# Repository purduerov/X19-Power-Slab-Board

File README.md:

# Purdue ROV KiCad Board Template

Starter template for new PCB designs in Purdue ROV. Pre-configured with the team component library submodule, automatic Git clean filters, isolation rules, and CI/CD validation.

---

## 🚀 Quickstart: Opening the Project (Recommended)

**Always open the project using the 1-click launcher:**

* **Windows:** Double-click `LAUNCH_KICAD.bat`
* **macOS / Linux:** Run `./LAUNCH_KICAD.sh`

### What the Launcher Does Automatically:
1. ⚙️ **Configures Git Hooks & Clean Filters:** Sets up Git to strip volatile viewport/zoom coordinates on every commit, preventing merge conflicts.
2. 🔄 **Auto-Updates Component Library:** Pulls the freshest symbols, footprints, and 3D models from `purdue-rov-kicad-lib` before opening.
3. 📐 **Opens KiCad:** Launches the project file with all 6 central library categories pre-linked.

---

## Creating a New Board Repository

1. In GitHub, click **Use this template** > **Create a new repository**.
2. Name the repo to match the board function (e.g. `thruster-interface-board`).
3. Clone recursively so submodules are pulled:
   ```bash
   git clone --recursive https://github.com/purduerov/<your-repo-name>.git
   cd <your-repo-name>
   ```
   If cloned without `--recursive`, initialize the submodule:
   ```bash
   git submodule update --init --recursive
   ```

4. Rename the project files (`board-template.kicad_*`) to match your project name.

## Central Component Library & Manager GUI

The template is pre-configured with project-level library tables (`sym-lib-table` and `fp-lib-table`) pointing to `purdue-rov-kicad-lib`:
- `rov_passives`: Resistors, capacitors, inductors, crystals
- `rov_power`: Voltage regulators, buck/boost converters, MOSFETs, diodes
- `rov_logic`: MCUs, logic ICs, op-amps, level shifters, transceivers
- `rov_connectors`: Power terminals, XT60/XT30, headers, USB, JST connectors
- `rov_sensors`: IMUs, temperature, pressure sensors
- `rov_mech`: Mounting holes, standoffs, test points

### Launching the Library Manager GUI
To browse parts, inspect footprints, edit properties, or add/delete components in the shared library:
- **Windows:** Double-click `libs\purdue-rov-kicad-lib\LIBRARY_MANAGER.bat`
- **macOS / Linux:** Run `./libs/purdue-rov-kicad-lib/LIBRARY_MANAGER.sh`

## Design Rules & Clearances

- Clearance rules (JLCPCB 4-layer rules) are defined in `X19-Power-Slab-Board.kicad_dru`.
- High-power thruster nets require a minimum 2.0 mm clearance from low-voltage logic (3.3V / 5V).

## Automated CI/CD & DevOps Preflight Checks

All CI/CD automation and tooling are centralized in [`purduerov/pcb-devops`](https://github.com/purduerov/pcb-devops):
1. **Automated Git Clean Filters:** Configured automatically by `.githooks/pre-commit` to prevent viewport/zoom merge noise.
2. **KiCad Symbol Linting:** Validates mandatory fields (`MPN`, `Manufacturer`, `Category`, `DigiKey`, `Datasheet`, `Temp_Range`) on all library components.
3. **ERC & DRC Validation:** Executes Electrical and Design Rules Checks via KiBot in GitHub Actions.
4. **Artifact Generation:** Automatically exports Schematic PDFs, Board Layout PDFs, and Interactive HTML BOMs on every pull request.

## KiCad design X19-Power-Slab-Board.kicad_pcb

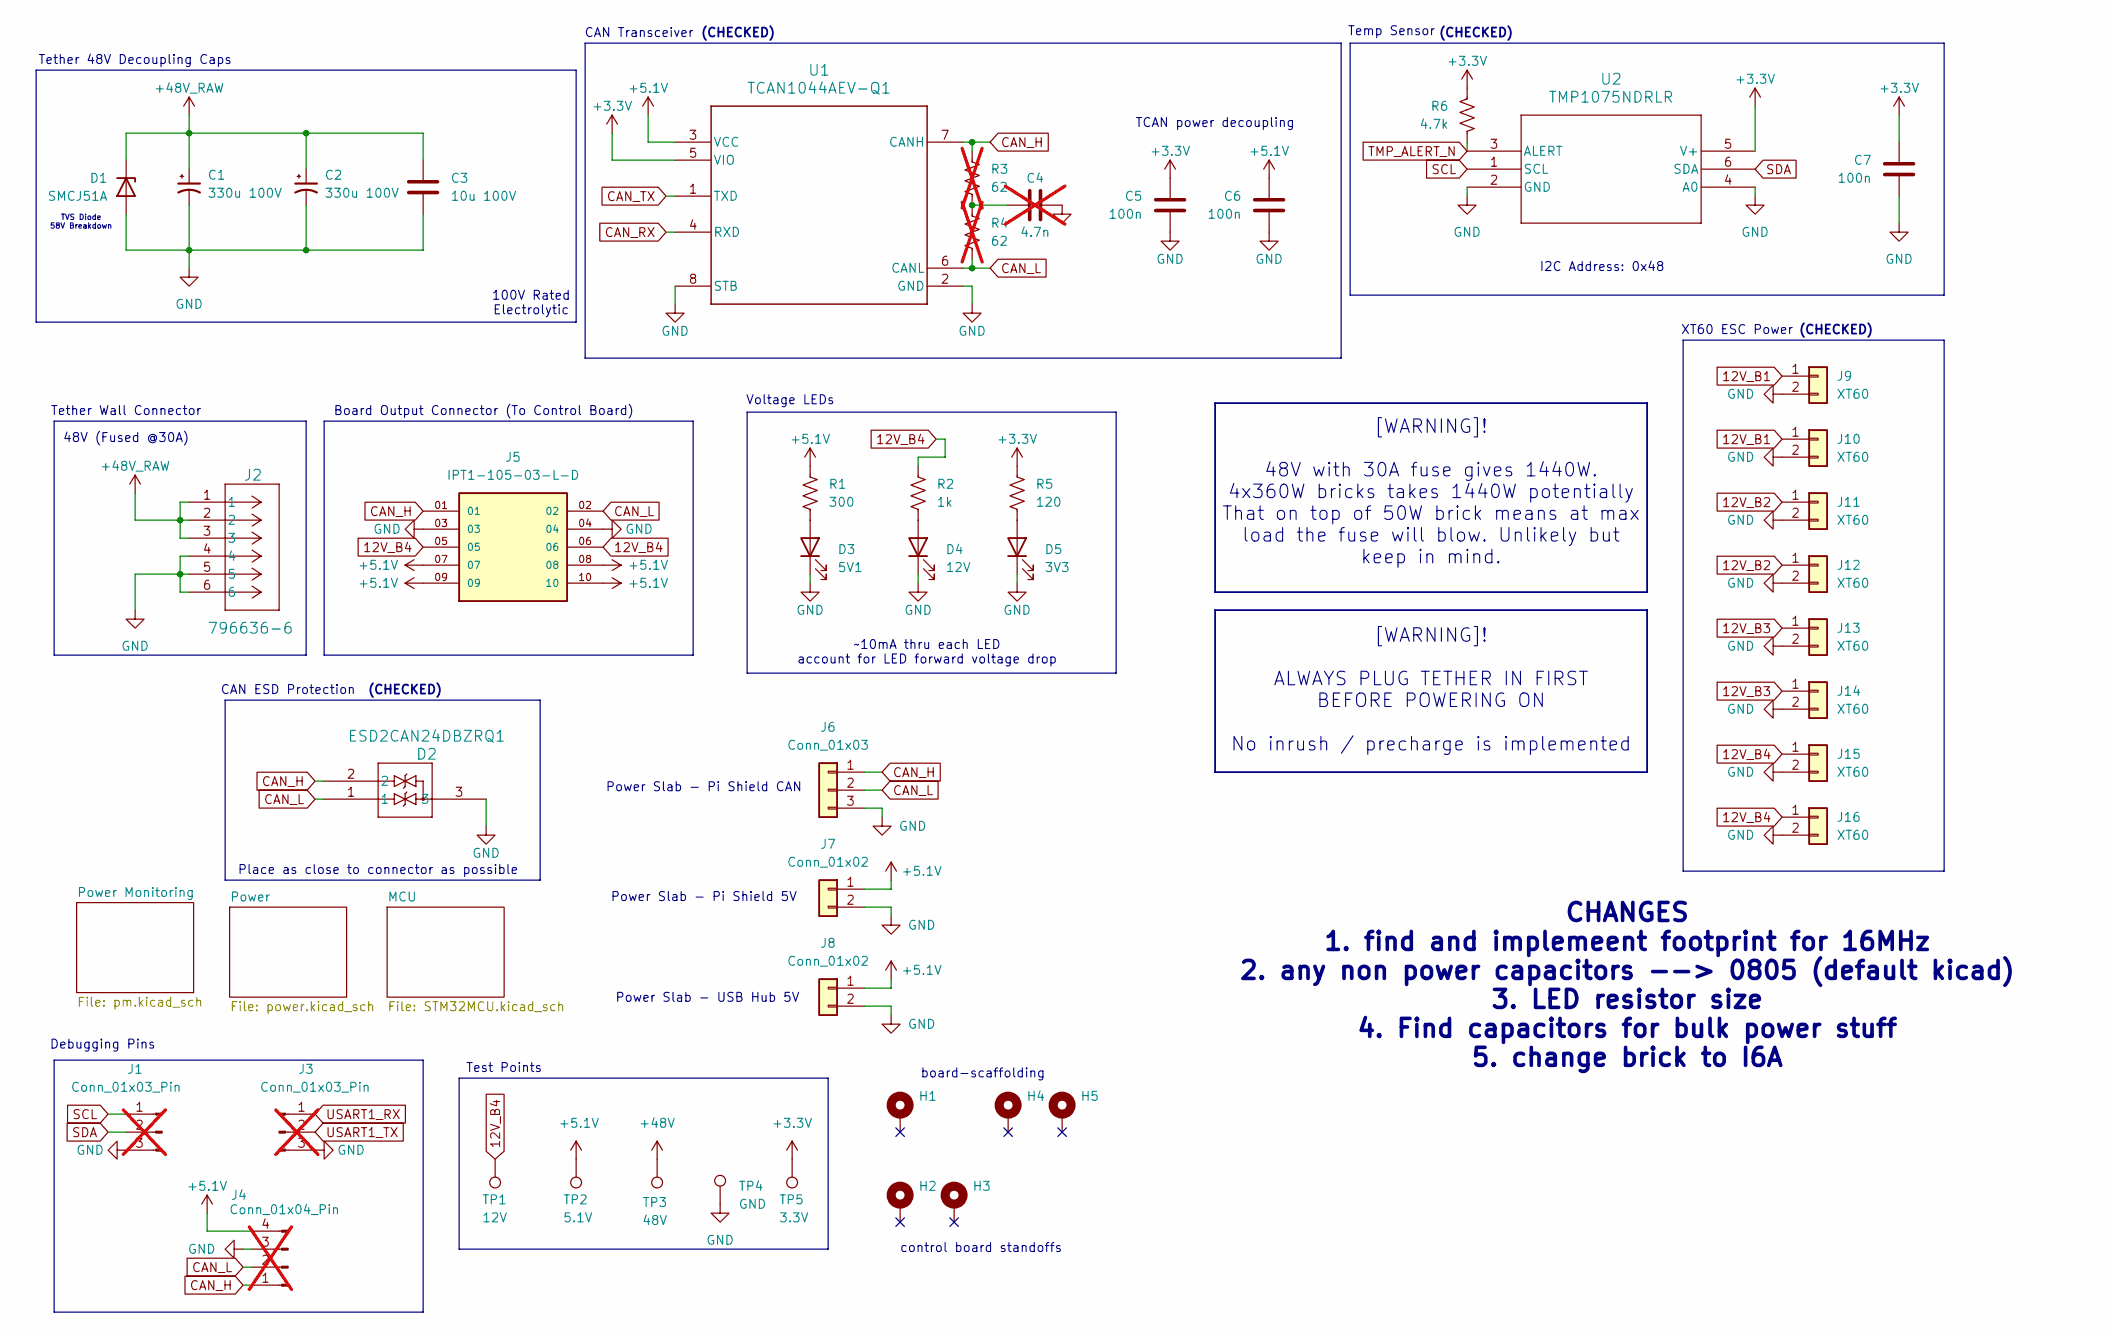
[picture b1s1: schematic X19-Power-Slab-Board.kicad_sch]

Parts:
C1, C2: 330u 100V; CP_Radial_D13.0mm_P5.00mm; Part Number 860040878008
C3: 10u 100V; C_1210_3225Metric; Part Number GMC32X7R106K100NT
C4: 4.7n; C_0603_1608Metric_Pad1.08x0.95mm_HandSolder; Part Number CC0603KRX7R9BB472; not fitted
C5, C6, C7: 100n; C_0603_1608Metric_Pad1.08x0.95mm_HandSolder; Part Number CC0603KRX7R8BB104
D1: SMCJ51A; D_SMC; Part Number SMCJ51A
D2: ESD2CAN24DBZRQ1; SOT-23_Handsoldering; Part Number ESD2CAN24DBZRQ1
D3: 5V1; LED_0603_1608Metric_Pad1.05x0.95mm_HandSolder; Part Number LTST-C190GKT
D4: 12V; LED_0603_1608Metric_Pad1.05x0.95mm_HandSolder; Part Number LTST-C190KRKT
D5: 3V3; LED_0603_1608Metric_Pad1.05x0.95mm_HandSolder; Part Number LTST-C190YKT
H1, H4, H5: MountingHole_Pad; MountingHole_3.5mm_Pad
H2, H3: MountingHole_Pad; MountingHole_2.7mm_M2.5_Pad
J1, J3: Conn_01x03_Pin; PinHeader_1x03_P2.54mm_Vertical; Part Number Generic 2.54mm Pinheader; not fitted
J2: 796636-6; CON6_P5MM_VER_TERM-BLK_TYC; Part Number 796636-6
J4: Conn_01x04_Pin; PinHeader_1x04_P2.54mm_Vertical; Part Number Generic 2.54mm Pinheader; not fitted
J5: IPT1-105-03-L-D; SAMTEC_IPT1-105-01-S-D; PARTREV R
J6: Conn_01x03; Molex_Micro-Fit_3.0_43650-0300_1x03_P3.00mm_Horizontal; Part Number 43650-0300
J7, J8: Conn_01x02; Molex_Micro-Fit_3.0_43650-0200_1x02_P3.00mm_Horizontal; Part Number 43650-0200
J9, J10, J11, J12, J13, J14, J15, J16: XT60; AMASS_XT60PB-M; Part Number 1568-10474-ND
R1: 300; R_0603_1608Metric_Pad0.98x0.95mm_HandSolder; Part Number RC0603FR-07300RL
R2: 1k; R_0603_1608Metric_Pad0.98x0.95mm_HandSolder; Part Number RC0603FR-071KL
R3, R4: 62; R_0603_1608Metric_Pad0.98x0.95mm_HandSolder; Part Number RC0603FR-0762RL; not fitted
R5: 120; R_0603_1608Metric_Pad0.98x0.95mm_HandSolder; Part Number RC0603FR-07120RL
R6: 4.7k; R_0603_1608Metric_Pad0.98x0.95mm_HandSolder; Part Number RC0603FR-074K7L
TP1: 12V; TestPoint_Pad_D4.0mm
TP2: 5.1V; TestPoint_Pad_D2.5mm
TP3: 48V; TestPoint_Pad_D4.0mm
TP4: GND; TestPoint_Pad_D2.5mm
TP5: 3.3V; TestPoint_Pad_D2.5mm
U1: TCAN1044AEV-Q1; SOIC-8_3.9x4.9mm_P1.27mm; Part Number TCAN1044AEVDRQ1
U2: TMP1075NDRLR; SOT5X3-6_DRL_TEX; Part Number TMP1075NDRLR

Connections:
12V_B1: J9.1, J10.1; also elsewhere on the board
12V_B2: J11.1, J12.1; also elsewhere on the board
12V_B3: J13.1, J14.1; also elsewhere on the board
12V_B4: J5.05, J5.06, J15.1, J16.1, R2.2, TP1.1 (1_1); also elsewhere on the board
+3.3V: C5.1, C7.1, R5.2, R6.1, TP5.1 (1_1), U1.5 (VIO), U2.5 (V+); also elsewhere on the board
+5.1V: C6.1, J4.4, J5.07, J5.08, J5.09, J5.10, J7.1, J8.1, R1.2, TP2.1 (1_1), U1.3 (VCC); also elsewhere on the board
+48V: TP3.1 (1_1); also elsewhere on the board
+48V_RAW: C1.1, C2.1, C3.1, D1.1 (K), J2.1, J2.2, J2.3; also elsewhere on the board
CAN_H: D2.2, J4.1, J5.01, J6.1, R3.1, U1.7 (CANH)
CAN_L: D2.1, J4.2, J5.02, J6.2, R4.2, U1.6 (CANL)
CAN_RX: U1.4 (RXD); also elsewhere on the board
CAN_TX: U1.1 (TXD); also elsewhere on the board
GND: C1.2, C2.2, C3.2, C4.2, C5.2, C6.2, C7.2, D1.2 (A), D2.3, D3.1 (K), D4.1 (K), D5.1 (K), J1.3, J2.4, J2.5, J2.6, J3.3, J4.3, J5.03, J5.04, J6.3, J7.2, J8.2, J9.2, J10.2, J11.2, J12.2, J13.2, J14.2, J15.2, J16.2, TP4.1 (1_1), U1.2 (GND), U1.8 (STB), U2.2 (GND), U2.4 (A0); also elsewhere on the board
unnamed: C4.1, R3.2, R4.1
unnamed: D3.2 (A), R1.1
unnamed: D4.2 (A), R2.1
unnamed: D5.2 (A), R5.1
SCL: J1.1, U2.1 (SCL); also elsewhere on the board
SDA: J1.2, U2.6 (SDA); also elsewhere on the board
TMP_ALERT_N: R6.2, U2.3 (ALERT); also elsewhere on the board
USART1_RX: J3.1; also elsewhere on the board
USART1_TX: J3.2; also elsewhere on the board

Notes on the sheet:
TCAN power decoupling
(CHECKED)
100V Rated Electrolytic
XT60 ESC Power
CAN Transceiver
control board standoffs
I2C Address: 0x48
Power Slab - Pi Shield CAN
[WARNING]! 48V with 30A fuse gives 1440W. 4x360W bricks takes 1440W potentially That on top of 50W brick means at max load the fuse will blow. Unlikely but keep in mind.
Place as close to connector as possible
Temp Sensor
Board Output Connector (To Control Board)
TVS Diode 58V Breakdown
~10mA thru each LED account for LED forward voltage drop
CAN ESD Protection
Tether 48V Decoupling Caps
Voltage LEDs
CHANGES 1. find and implemeent footprint for 16MHz 2. any non power capacitors --> 0805 (default kicad) 3. LED resistor size 4. Find capacitors for bulk power stuff 5. change brick to I6A
[WARNING]! ALWAYS PLUG TETHER IN FIRST BEFORE POWERING ON No inrush / precharge is implemented
board-scaffolding
Test Points
Debugging Pins
Power Slab - USB Hub 5V
Tether Wall Connector
48V (Fused @30A)
Power Slab - Pi Shield 5V

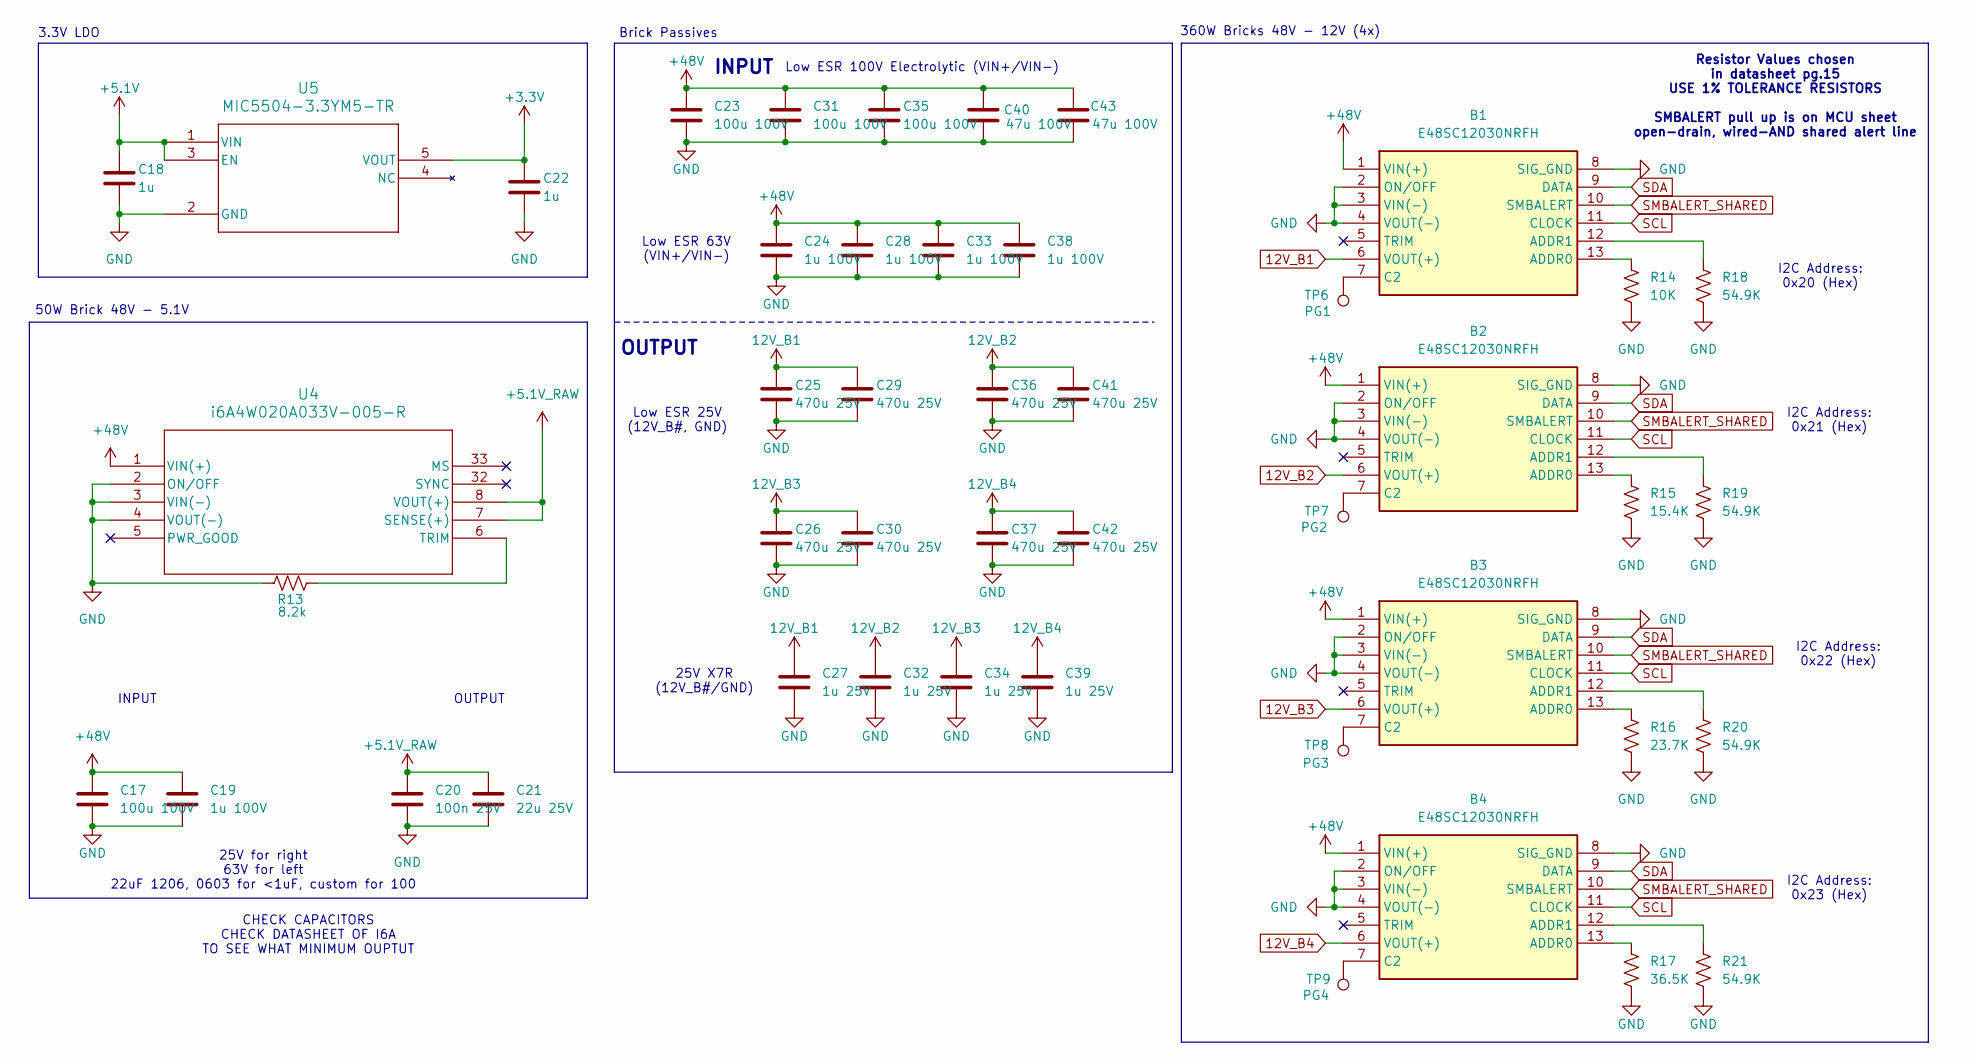
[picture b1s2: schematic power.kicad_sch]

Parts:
B1, B2, B3, B4: E48SC12030NRFH; Manufacturer_Part_Number E48SC12030NRFH
C17, C23, C31, C35: 100u 100V; CP_Radial_D10.0mm_P5.00mm; Part Number 100ZLH100MEFC10X20
C18, C22: 1u; C_0603_1608Metric_Pad1.08x0.95mm_HandSolder; Part Number CC0603KRX5R6BB105
C19, C24, C28, C33, C38: 1u 100V; C_0805_2012Metric_Pad1.18x1.45mm_HandSolder; Part Number CGA4J3X7S2A105M125AE
C20: 100n 25V; C_0603_1608Metric_Pad1.08x0.95mm_HandSolder; Part Number CC0603KRX7R8BB104
C21: 22u 25V; C_1206_3216Metric_Pad1.33x1.80mm_HandSolder; Part Number CC1206KKX5R8BB226
C25, C26, C29, C30, C36, C37, C41, C42: 470u 25V; CP_Radial_D10.0mm_P5.00mm; Part Number 25CZJ470M10X9
C27, C32, C34, C39: 1u 25V; C_0805_2012Metric_Pad1.18x1.45mm_HandSolder; Part Number CC0805KKX7R8BB105
C40, C43: 47u 100V; CP_Radial_D10.0mm_P5.00mm; Part Number UVZ2A470MPD
R13: 8.2k; R_0603_1608Metric_Pad0.98x0.95mm_HandSolder; Part Number RC0603FR-078K2L
R14: 10K; R_0603_1608Metric_Pad0.98x0.95mm_HandSolder; Part Number RC0603FR-0710KL
R15: 15.4K; R_0603_1608Metric_Pad0.98x0.95mm_HandSolder; Part Number RC0603FR-0715K4L
R16: 23.7K; R_0603_1608Metric_Pad0.98x0.95mm_HandSolder; Part Number RC0603FR-0723K7L
R17: 36.5K; R_0603_1608Metric_Pad0.98x0.95mm_HandSolder; Part Number RC0603FR-0736K5L
R18, R19, R20, R21: 54.9K; R_0603_1608Metric_Pad0.98x0.95mm_HandSolder; Part Number RC0603FR-0754K9L
TP6: PG1; TestPoint_Pad_D2.5mm
TP7: PG2; TestPoint_Pad_D2.5mm
TP8: PG3; TestPoint_Pad_D2.5mm
TP9: PG4; TestPoint_Pad_D2.5mm
U4: i6A4W020A033V-005-R; i6A4W_DIP_FULL_TDK; Part Number i6A4W020A033V-005-R
U5: MIC5504-3.3YM5-TR; SOT-23-5; Part Number MIC5504-3.3YM5-TR

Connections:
12V_B1: B1.6 (VOUT(+)), C25.1, C27.1, C29.1; also elsewhere on the board
12V_B2: B2.6 (VOUT(+)), C32.1, C36.1, C41.1; also elsewhere on the board
12V_B3: B3.6 (VOUT(+)), C26.1, C30.1, C34.1; also elsewhere on the board
12V_B4: B4.6 (VOUT(+)), C37.1, C39.1, C42.1; also elsewhere on the board
+3.3V: C22.1, U5.5 (VOUT); also elsewhere on the board
+5.1V: C18.1, U5.1 (VIN), U5.3 (EN); also elsewhere on the board
+5.1V_RAW: C20.1, C21.1, U4.7 (SENSE(+)), U4.8 (VOUT(+)); also elsewhere on the board
+48V: B1.1 (VIN(+)), B2.1 (VIN(+)), B3.1 (VIN(+)), B4.1 (VIN(+)), C17.1, C19.1, C23.1, C24.1, C28.1, C31.1, C33.1, C35.1, C38.1, C40.1, C43.1, U4.1 (VIN(+)); also elsewhere on the board
GND: B1.2 (ON/OFF), B1.3 (VIN(-)), B1.4 (VOUT(-)), B1.8 (SIG_GND), B2.2 (ON/OFF), B2.3 (VIN(-)), B2.4 (VOUT(-)), B2.8 (SIG_GND), B3.2 (ON/OFF), B3.3 (VIN(-)), B3.4 (VOUT(-)), B3.8 (SIG_GND), B4.2 (ON/OFF), B4.3 (VIN(-)), B4.4 (VOUT(-)), B4.8 (SIG_GND), C17.2, C18.2, C19.2, C20.2, C21.2, C22.2, C23.2, C24.2, C25.2, C26.2, C27.2, C28.2, C29.2, C30.2, C31.2, C32.2, C33.2, C34.2, C35.2, C36.2, C37.2, C38.2, C39.2, C40.2, C41.2, C42.2, C43.2, R13.1, R14.2, R15.2, R16.2, R17.2, R18.2, R19.2, R20.2, R21.2, U4.2 (ON/OFF), U4.3 (VIN(-)), U4.4 (VOUT(-)), U5.2 (GND); also elsewhere on the board
unnamed: B1.13 (ADDR0), R14.1
unnamed: B1.12 (ADDR1), R18.1
unnamed: B1.7 (C2), TP6.1 (1_1)
unnamed: B2.13 (ADDR0), R15.1
unnamed: B2.12 (ADDR1), R19.1
unnamed: B2.7 (C2), TP7.1 (1_1)
unnamed: B3.13 (ADDR0), R16.1
unnamed: B3.12 (ADDR1), R20.1
unnamed: B3.7 (C2), TP8.1 (1_1)
unnamed: B4.13 (ADDR0), R17.1
unnamed: B4.12 (ADDR1), R21.1
unnamed: B4.7 (C2), TP9.1 (1_1)
unnamed: R13.2, U4.6 (TRIM)
SCL: B1.11 (CLOCK), B2.11 (CLOCK), B3.11 (CLOCK), B4.11 (CLOCK); also elsewhere on the board
SDA: B1.9 (DATA), B2.9 (DATA), B3.9 (DATA), B4.9 (DATA); also elsewhere on the board
SMBALERT_SHARED: B1.10 (SMBALERT), B2.10 (SMBALERT), B3.10 (SMBALERT), B4.10 (SMBALERT); also elsewhere on the board

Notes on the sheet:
3.3V LDO
CHECK CAPACITORS CHECK DATASHEET OF I6A TO SEE WHAT MINIMUM OUPTUT
360W Bricks 48V - 12V (4x)
Brick Passives
Low ESR 63V (VIN+/VIN-)
50W Brick 48V - 5.1V
OUTPUT
INPUT
I2C Address: 0x21 (Hex)
Low ESR 100V Electrolytic (VIN+/VIN-)
I2C Address: 0x20 (Hex)
Low ESR 25V (12V_B#, GND)
25V for right 63V for left 22uF 1206, 0603 for <1uF, custom for 100
Resistor Values chosen in datasheet pg.15 USE 1% TOLERANCE RESISTORS SMBALERT pull up is on MCU sheet open-drain, wired-AND shared alert line
25V X7R (12V_B#/GND)
I2C Address: 0x22 (Hex)
I2C Address: 0x23 (Hex)

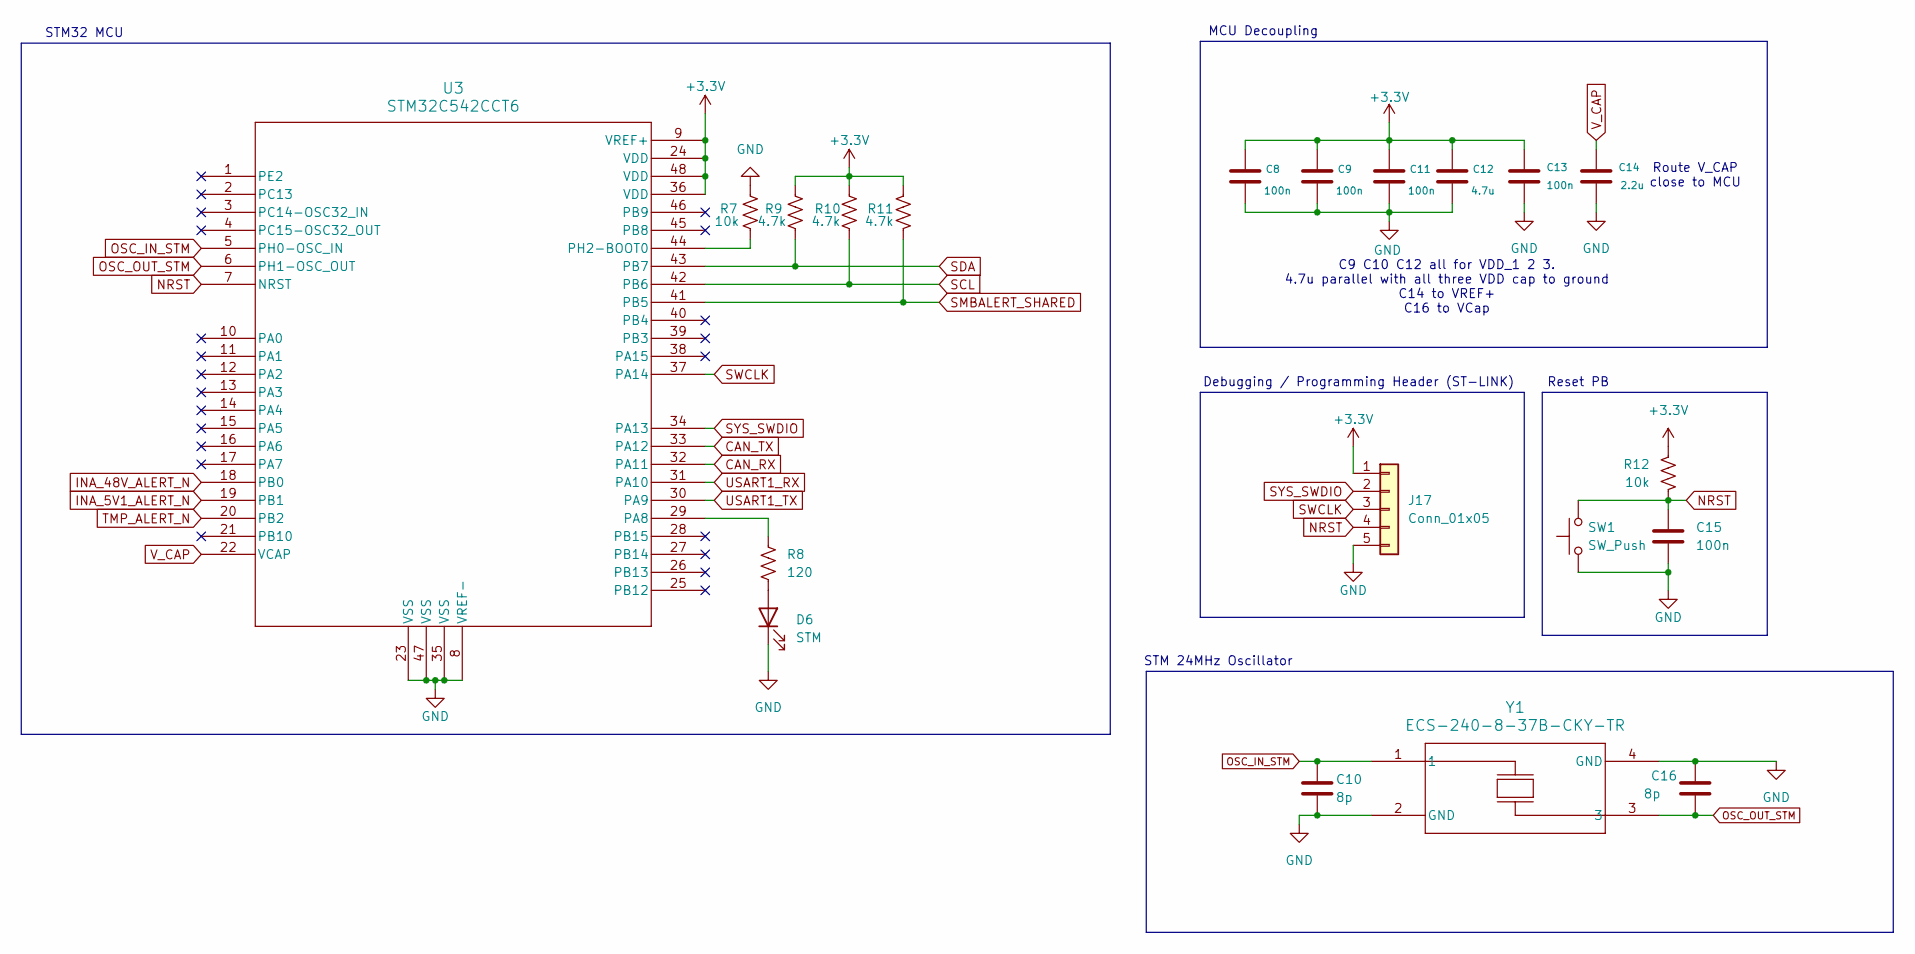
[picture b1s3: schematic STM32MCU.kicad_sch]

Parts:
C8, C9, C11, C13, C15: 100n; C_0603_1608Metric_Pad1.08x0.95mm_HandSolder; Part Number CC0603KRX7R8BB104
C10, C16: 8p; C_0603_1608Metric_Pad1.08x0.95mm_HandSolder; Part Number CC0603DRNPO9BN8R0
C12: 4.7u; C_0603_1608Metric_Pad1.08x0.95mm_HandSolder; Part Number CC0603KRX5R6BB475
C14: 2.2u; C_0603_1608Metric_Pad1.08x0.95mm_HandSolder; Part Number CC0603KRX5R6BB225
D6: STM; LED_0603_1608Metric_Pad1.05x0.95mm_HandSolder; Part Number LTST-C190GKT
J17: Conn_01x05; PinHeader_1x05_P2.54mm_Vertical; Part Number Generic 2.54mm Pinheader
R7, R12: 10k; R_0603_1608Metric_Pad0.98x0.95mm_HandSolder; Part Number RC0603FR-0710KL
R8: 120; R_0603_1608Metric_Pad0.98x0.95mm_HandSolder; Part Number RC0603FR-07120RL
R9, R10, R11: 4.7k; R_0603_1608Metric_Pad0.98x0.95mm_HandSolder; Part Number RC0603FR-074K7L
SW1: SW_Push; SW_SPST_B3U-1000P; Part Number B3U-1000P
U3: STM32C542CCT6; LQFP-48_7x7mm_P0.5mm; Part Number STM32C542CCT6
Y1: ECS-240-8-37B-CKY-TR; Crystal_SMD_2016-4Pin_2.0x1.6mm; Part Number ECS-240-8-37B-CKY-TR

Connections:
+3.3V: C8.1, C9.1, C11.1, C12.1, C13.1, J17.1, R9.2, R10.2, R11.1, R12.1, U3.9 (VREF+), U3.24 (VDD), U3.36 (VDD), U3.48 (VDD); also elsewhere on the board
CAN_RX: U3.32 (PA11); also elsewhere on the board
CAN_TX: U3.33 (PA12); also elsewhere on the board
GND: C8.2, C9.2, C10.1, C11.2, C12.2, C13.2, C14.2, C15.2, C16.1, D6.1 (K), J17.5, R7.2, SW1.1, U3.8 (VREF-), U3.23 (VSS), U3.35 (VSS), U3.47 (VSS), Y1.2 (GND), Y1.4 (GND); also elsewhere on the board
INA_5V1_ALERT_N: U3.19 (PB1); also elsewhere on the board
INA_48V_ALERT_N: U3.18 (PB0); also elsewhere on the board
NRST: C15.1, J17.4, R12.2, SW1.2, U3.7 (NRST)
unnamed: D6.2 (A), R8.2
unnamed: R8.1, U3.29 (PA8)
unnamed: R7.1, U3.44 (PH2-BOOT0)
OSC_IN_STM: C10.2, U3.5 (PH0-OSC_IN), Y1.1
OSC_OUT_STM: C16.2, U3.6 (PH1-OSC_OUT), Y1.3
SCL: R10.1, U3.42 (PB6); also elsewhere on the board
SDA: R9.1, U3.43 (PB7); also elsewhere on the board
SMBALERT_SHARED: R11.2, U3.41 (PB5); also elsewhere on the board
SWCLK: J17.3, U3.37 (PA14)
SYS_SWDIO: J17.2, U3.34 (PA13)
TMP_ALERT_N: U3.20 (PB2); also elsewhere on the board
USART1_RX: U3.31 (PA10); also elsewhere on the board
USART1_TX: U3.30 (PA9); also elsewhere on the board
V_CAP: C14.1, U3.22 (VCAP)

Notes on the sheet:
C9 C10 C12 all for VDD_1 2 3. 4.7u parallel with all three VDD cap to ground C14 to VREF+ C16 to VCap
Reset PB
Debugging / Programming Header (ST-LINK)
STM32 MCU
STM 24MHz Oscillator
MCU Decoupling
Route V_CAP close to MCU

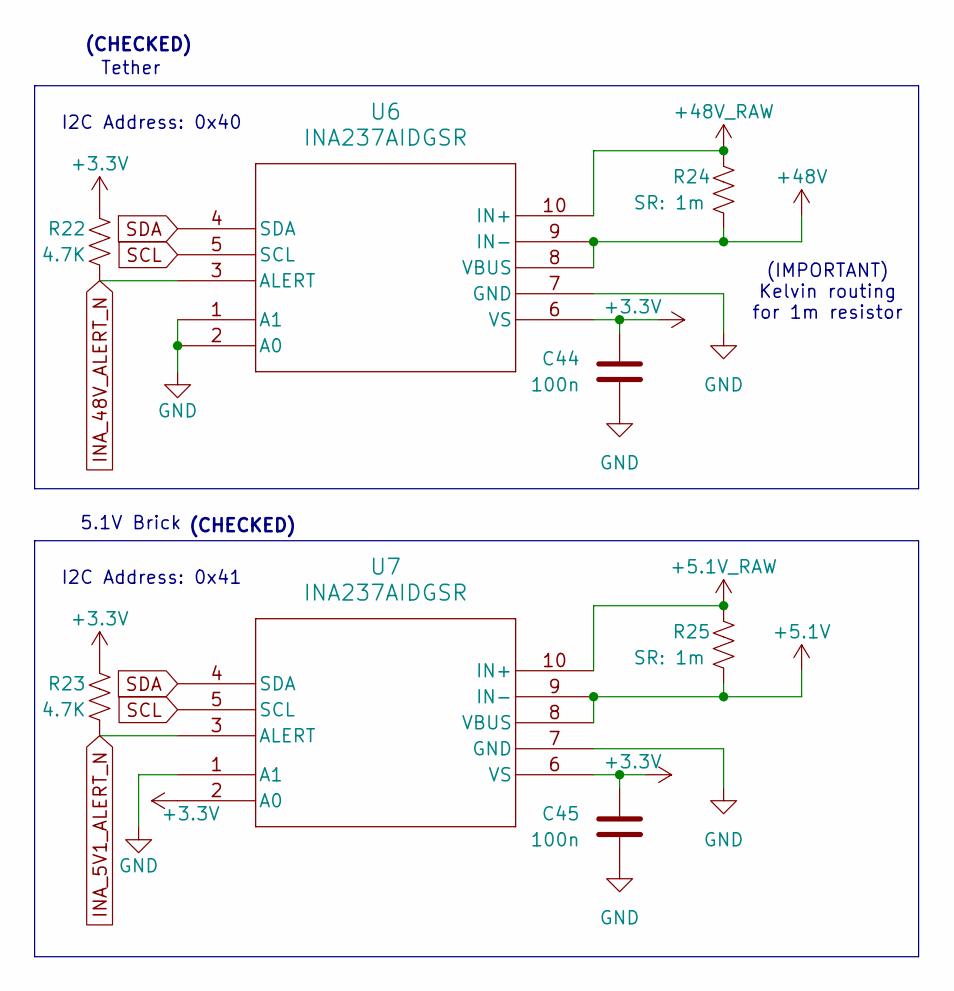
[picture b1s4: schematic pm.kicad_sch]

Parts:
C44, C45: 100n; C_0603_1608Metric_Pad1.08x0.95mm_HandSolder; Part Number CC0603KRX7R8BB104
R22, R23: 4.7K; R_0603_1608Metric_Pad0.98x0.95mm_HandSolder; Part Number RC0603FR-074K7L
R24, R25: SR: 1m; R_2512_6332Metric_Pad1.40x3.35mm_HandSolder; Part Number WSLF25121L000FEA
U6, U7: INA237AIDGSR; TSSOP-10_3x3mm_P0.5mm; Part Number INA237AIDGSR

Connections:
+3.3V: C44.1, C45.1, R22.1, R23.1, U6.6 (VS), U7.2 (A0), U7.6 (VS); also elsewhere on the board
+5.1V: R25.2, U7.8 (VBUS), U7.9 (IN-); also elsewhere on the board
+5.1V_RAW: R25.1, U7.10 (IN+); also elsewhere on the board
+48V: R24.2, U6.8 (VBUS), U6.9 (IN-); also elsewhere on the board
+48V_RAW: R24.1, U6.10 (IN+); also elsewhere on the board
GND: C44.2, C45.2, U6.1 (A1), U6.2 (A0), U6.7 (GND), U7.1 (A1), U7.7 (GND); also elsewhere on the board
INA_5V1_ALERT_N: R23.2, U7.3 (ALERT); also elsewhere on the board
INA_48V_ALERT_N: R22.2, U6.3 (ALERT); also elsewhere on the board
SCL: U6.5 (SCL), U7.5 (SCL); also elsewhere on the board
SDA: U6.4 (SDA), U7.4 (SDA); also elsewhere on the board

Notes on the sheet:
Tether
(IMPORTANT) Kelvin routing for 1m resistor
(CHECKED)
5.1V Brick
I2C Address: 0x41
I2C Address: 0x40

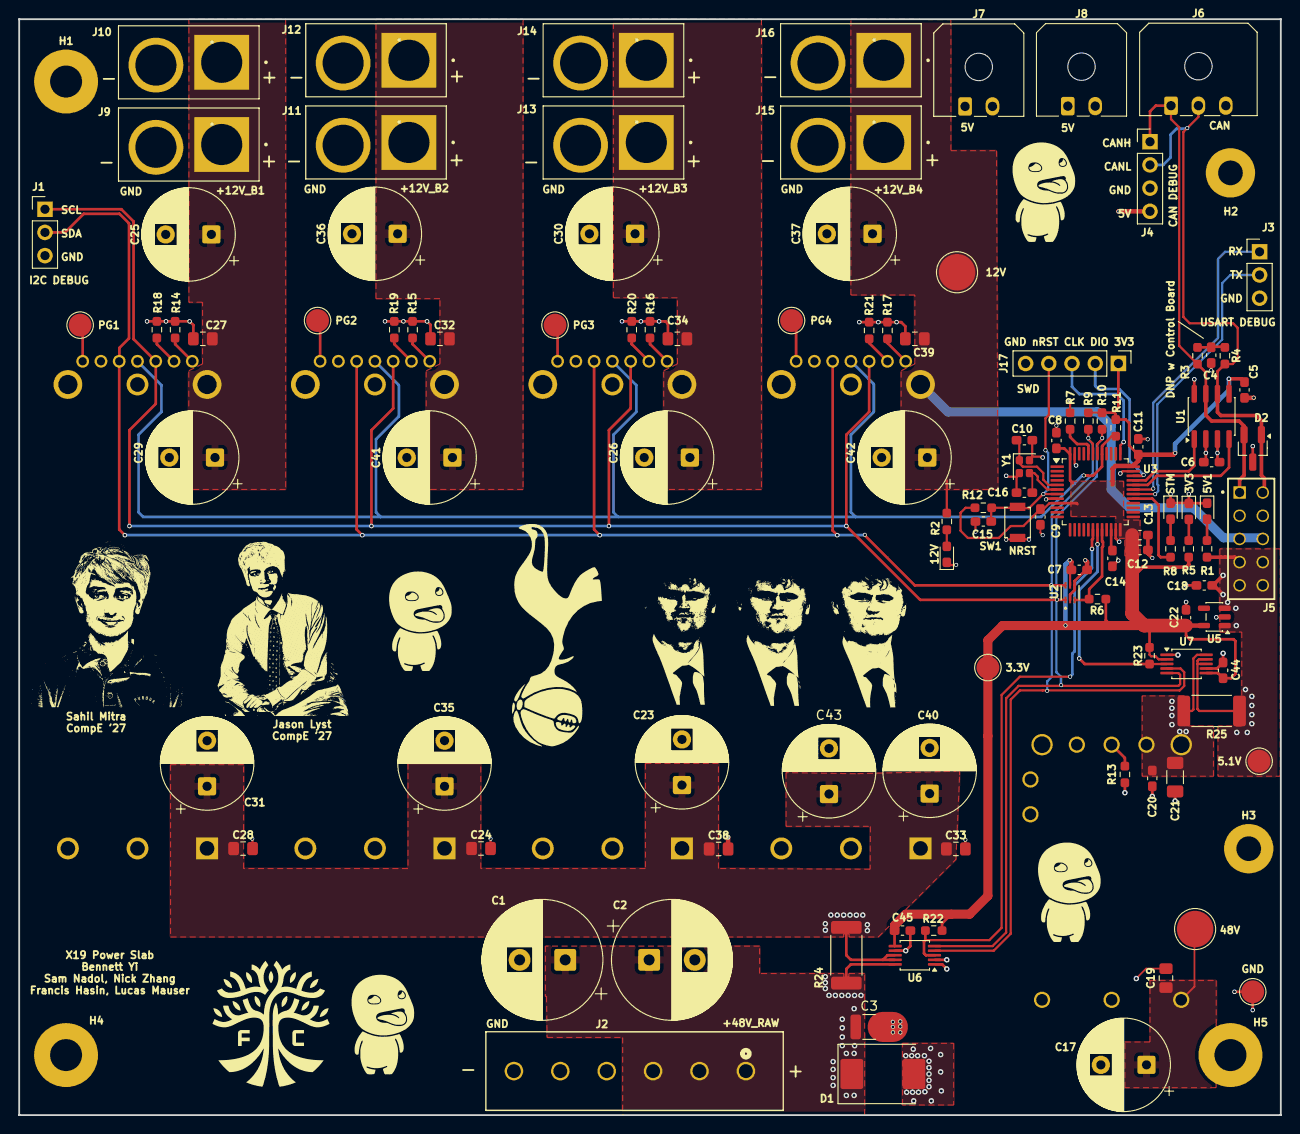
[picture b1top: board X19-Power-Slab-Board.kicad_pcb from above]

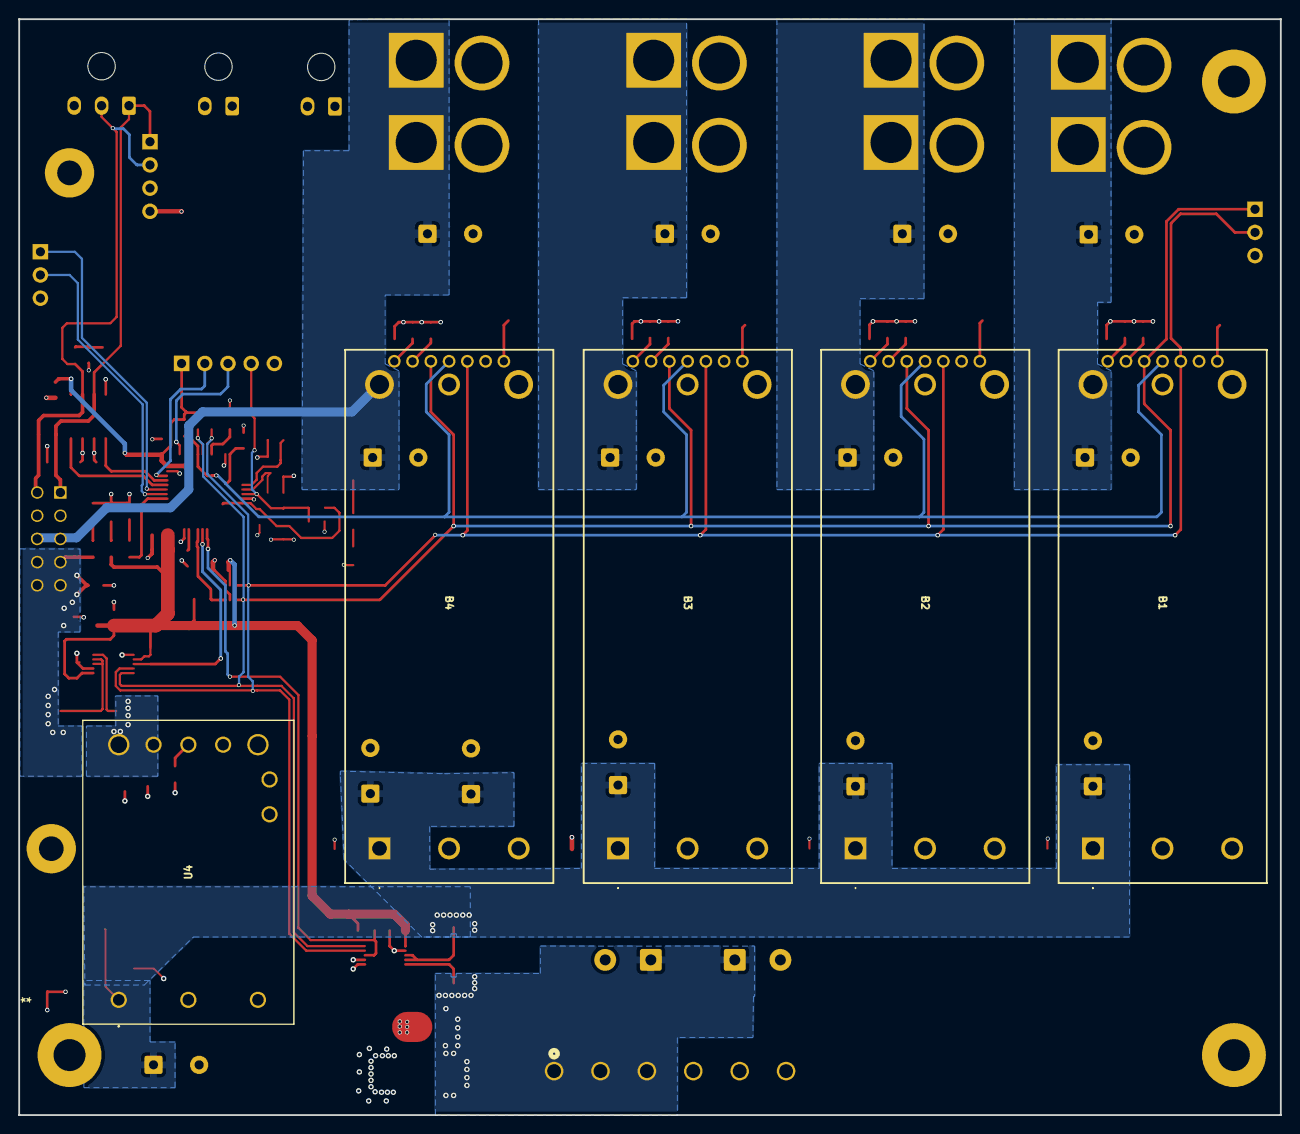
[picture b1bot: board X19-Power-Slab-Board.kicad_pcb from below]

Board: 4 copper layers, 138.1 x 120.0 mm, 120 parts (5 on the bottom side), 48 nets.

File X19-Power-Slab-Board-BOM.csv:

Row,Description,Part,References,Value,Footprint,Quantity Per PCB,Status,Datasheet,AVAILABILITY,MAXIMUM_PACKAGE_HEIGHT,MF,MP,PACKAGE,PRICE,Part Number,Sim.Pins,PARTREV,STANDARD,MANUFACTURER,Height,Mouser Part Number,Mouser Price/Stock,Manufacturer_Name,Manufacturer_Part_Number
1,"Isolated DC/DC Converters - Through Hole DC/DC Converter, 1/8 Brick, 12Vout, 30A",E48SC12030NRFH,B1 B2 B3 B4,E48SC12030NRFH,E48SC12030NRFH,4, ,https://filecenter.deltaww.com/products/download/01/0102/dat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,,,,,,,E48SC12030NRFH,,,,,13.2,,,Delta Electronics,E48SC12030NRFH
2,Unpolarized capacitor,C,C10 C16,8p,C_0603_1608Metric_Pad1.08x0.95mm_HandSolder,2, ,,,,,,,,CC0603DRNPO9BN8R0,,,,,,,,,
3,Unpolarized capacitor,C,C5 C6 C7 C8 C9 C11 C13 C15 C20 C44 C45,100n,C_0603_1608Metric_Pad1.08x0.95mm_HandSolder,11, ,,,,,,,,CC0603KRX7R8BB104,,,,,,,,,
4,Unpolarized capacitor,C,C18 C22,1u,C_0603_1608Metric_Pad1.08x0.95mm_HandSolder,2, ,,,,,,,,CC0603KRX5R6BB105,,,,,,,,,
5,Unpolarized capacitor,C,C19 C24 C27 C28 C32 C33 C34 C38 C39,1u 100V,C_0805_2012Metric_Pad1.18x1.45mm_HandSolder,9, ,,,,,,,,CGA4J3X7S2A105M125AE CC0805KKX7R8BB105,,,,,,,,,
6,Unpolarized capacitor,C,C14,2.2u,C_0603_1608Metric_Pad1.08x0.95mm_HandSolder,1, ,,,,,,,,CC0603KRX5R6BB225,,,,,,,,,
7,Unpolarized capacitor,C,C12,4.7u,C_0603_1608Metric_Pad1.08x0.95mm_HandSolder,1, ,,,,,,,,CC0603KRX5R6BB475,,,,,,,,,
8,Unpolarized capacitor,C,C3,10u 100V,C_1210_3225Metric,1, ,,,,,,,,GMC32X7R106K100NT,,,,,,,,,
9,Unpolarized capacitor,C,C21,22u 25V,C_1206_3216Metric_Pad1.33x1.80mm_HandSolder,1, ,,,,,,,,CC1206KKX5R8BB226,,,,,,,,,
10,Unpolarized capacitor,C,C40 C43,47u 100V,CP_Radial_D10.0mm_P5.00mm,2, ,,,,,,,,UVZ2A470MPD,,,,,,,,,
11,Unpolarized capacitor,C,C17 C23 C31 C35,100u 100V,CP_Radial_D10.0mm_P5.00mm,4, ,,,,,,,,100ZLH100MEFC10X20,,,,,,,,,
12,"Polarized capacitor, small US symbol",C_Polarized_Small_US,C1 C2,330u 100V,CP_Radial_D13.0mm_P5.00mm,2, ,,,,,,,,860040878008,,,,,,,,,
13,Unpolarized capacitor,C,C25 C26 C29 C30 C36 C37 C41 C42,470u 25V,CP_Radial_D10.0mm_P5.00mm,8, ,,,,,,,,25CZJ470M10X9,,,,,,,,,
14,Light emitting diode,LED,D4,12V,LED_0603_1608Metric_Pad1.05x0.95mm_HandSolder,1, ,,,,,,,,LTST-C190KRKT,1=K 2=A,,,,,,,,
15,Light emitting diode,LED,D5,3V3,LED_0603_1608Metric_Pad1.05x0.95mm_HandSolder,1, ,,,,,,,,LTST-C190YKT,1=K 2=A,,,,,,,,
16,Light emitting diode,LED,D3,5V1,LED_0603_1608Metric_Pad1.05x0.95mm_HandSolder,1, ,,,,,,,,LTST-C190GKT,1=K 2=A,,,,,,,,
17,,ESD2CAN24DBZRQ1,D2,ESD2CAN24DBZRQ1,SOT-23_Handsoldering,1, ,ESD2CAN24DBZRQ1,,,,,,,ESD2CAN24DBZRQ1,,,,,,,,,
18,"ESD Protection Diode, DO-214AB, SMC",ESD5Zxx,D1,SMCJ51A,D_SMC,1, ,https://www.littelfuse.com/assetdocs/littelfuse_tvs_diode_sm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,,,,,,,SMCJ51A,,,,,,,,,
19,Light emitting diode,LED,D6,STM,LED_0603_1608Metric_Pad1.05x0.95mm_HandSolder,1, ,,,,,,,,LTST-C190GKT,1=K 2=A,,,,,,,,
20,,796636-6,J2,796636-6,CON6_P5MM_VER_TERM-BLK_TYC,1, ,https://www.te.com/commerce/DocumentDelivery/DDEController?A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,,,,,,,796636-6,,,,,,,,,
21,"Generic connector, single row, 01x02, script generated (kicad-library-utils/schlib/autogen/connector/)",Conn_01x02,J7 J8,Conn_01x02,Molex_Micro-Fit_3.0_43650-0200_1x02_P3.00mm_Horizontal,2, ,,,,,,,,43650-0200,,,,,,,,,
22,"Generic connector, single row, 01x03, script generated (kicad-library-utils/schlib/autogen/connector/)",Conn_01x03,J6,Conn_01x03,Molex_Micro-Fit_3.0_43650-0300_1x03_P3.00mm_Horizontal,1, ,,,,,,,,43650-0300,,,,,,,,,
23,,IPT1-105-01-S-D,J5,IPT1-105-01-S-D,SAMTEC_IPT1-105-01-S-D,1, ,,,,,,,,IPT1-105-01-S-D,,R,Manufacturer Recommendations,Samtec,,,,,
24,"Generic connector, single row, 01x02, script generated (kicad-library-utils/schlib/autogen/connector/)",Conn_01x02,J9 J10 J11 J12 J13 J14 J15 J16,XT60,AMASS_XT60PB-M,8, ,,,,,,,,1568-10474-ND,,,,,,,,,
25,"Resistor, US symbol",R_US,R5 R8,120,R_0603_1608Metric_Pad0.98x0.95mm_HandSolder,2, ,,,,,,,,RC0603FR-07120RL,,,,,,,,,
26,"Resistor, US symbol",R_US,R1,300,R_0603_1608Metric_Pad0.98x0.95mm_HandSolder,1, ,,,,,,,,RC0603FR-07300RL,,,,,,,,,
27,"Resistor, US symbol",R_US,R2,1k,R_0603_1608Metric_Pad0.98x0.95mm_HandSolder,1, ,,,,,,,,RC0603FR-071KL,,,,,,,,,
28,"Resistor, US symbol",R_US,R6 R9 R10 R11 R22 R23,4.7k,R_0603_1608Metric_Pad0.98x0.95mm_HandSolder,6, ,,,,,,,,RC0603FR-074K7L,,,,,,,,,
29,"Resistor, US symbol",R_US,R13,8.2k,R_0603_1608Metric_Pad0.98x0.95mm_HandSolder,1, ,,,,,,,,RC0603FR-078K2L,,,,,,,,,
30,"Resistor, US symbol",R_US,R7 R12 R14,10k,R_0603_1608Metric_Pad0.98x0.95mm_HandSolder,3, ,,,,,,,,RC0603FR-0710KL,,,,,,,,,
31,"Resistor, US symbol",R_US,R15,15.4K,R_0603_1608Metric_Pad0.98x0.95mm_HandSolder,1, ,,,,,,,,RC0603FR-0715K4L,,,,,,,,,
32,"Resistor, US symbol",R_US,R16,23.7K,R_0603_1608Metric_Pad0.98x0.95mm_HandSolder,1, ,,,,,,,,RC0603FR-0723K7L,,,,,,,,,
33,"Resistor, US symbol",R_US,R17,36.5K,R_0603_1608Metric_Pad0.98x0.95mm_HandSolder,1, ,,,,,,,,RC0603FR-0736K5L,,,,,,,,,
34,"Resistor, US symbol",R_US,R18 R19 R20 R21,54.9K,R_0603_1608Metric_Pad0.98x0.95mm_HandSolder,4, ,,,,,,,,RC0603FR-0754K9L,,,,,,,,,
35,"Resistor, US symbol",R_US,R24 R25,SR: 1m,R_2512_6332Metric_Pad1.40x3.35mm_HandSolder,2, ,,,,,,,,WSLF25121L000FEA,,,,,,,,,
36,"Push button switch, generic, two pins",SW_Push,SW1,SW_Push,SW_SPST_B3U-1000P,1, ,,,,,,,,B3U-1000P,,,,,,,,,
37,,INA237AIDGSR,U6 U7,INA237AIDGSR,TSSOP-10_3x3mm_P0.5mm,2, ,https://www.ti.com/lit/gpn/ina237,,,,,,,INA237AIDGSR,,,,,,,,,
38,,MIC5504-3.3YM5-TR,U5,MIC5504-3.3YM5-TR,SOT-23-5,1, ,MIC5504-3.3YM5-TR,,,,,,,MIC5504-3.3YM5-TR,,,,,,,,,
39,,STM32C542CCT6,U3,STM32C542CCT6,LQFP-48_7x7mm_P0.5mm,1, ,https://www.st.com/resource/en/datasheet/stm32c542cc.pdf,,,,,,,STM32C542CCT6,,,,,,,,,
40,,TCAN1044AVDRQ1,U1,TCAN1044AEV-Q1,SOIC-8_3.9x4.9mm_P1.27mm,1, ,https://www.ti.com/lit/ds/symlink/tcan1044aev-q1.pdf?ts=1718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,,,,,,,TCAN1044AEVDRQ1,,,,,,,,,
41,,TMP1075NDRLR,U2,TMP1075NDRLR,SOT5X3-6_DRL_TEX,1, ,https://www.ti.com/lit/gpn/tmp1075,,,,,,,TMP1075NDRLR,,,,,,,,,
42,,i6A4W020A033V-005-R,U4,i6A4W020A033V-005-R,i6A4W_DIP_FULL_TDK,1, ,https://product.tdk.com/system/files/dam/doc/product/power/s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,,,,,,,i6A4W020A033V-005-R,,,,,,,,,
43,,ABM8G-16.000MHZ-18-D2Y-T,Y1,ECS-240-8-37B-CKY-TR,Crystal_SMD_2016-4Pin_2.0x1.6mm,1, ,,,,,,,,ECS-240-8-37B-CKY-TR,,,,,,,,,





Project info:
Schematic:,X19-Power-Slab-Board
Variant:,default
Revision:,
Date:,2026-11-19_22-46-41
KiCad Version:,10.0.5-unknown-202607221313~667fa36054~ubuntu25.10.1
Statistics:
Component Groups:,45
Component Count:,102
Fitted Components:,99
Number of PCBs:,1
Total Components:,99
